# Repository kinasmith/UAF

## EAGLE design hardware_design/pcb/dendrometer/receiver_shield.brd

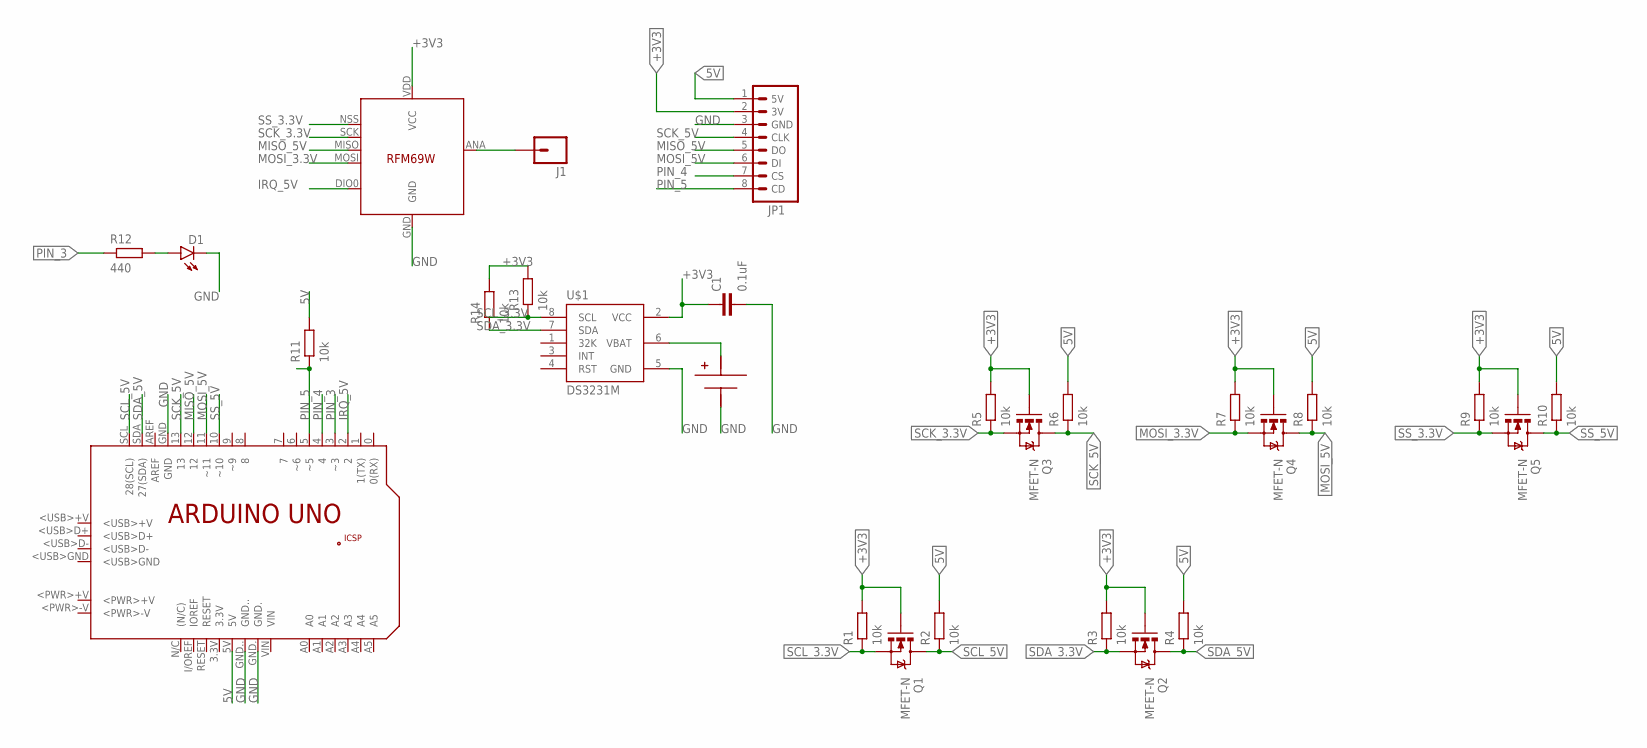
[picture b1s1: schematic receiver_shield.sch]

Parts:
C1: 0.1uF; C0603-N
D1: LED0603; LED-0603
J1: M01NOSILK-KIT; 1X01NS-KIT
JP1: SDCARD_BREAKOUT_HEADER1X08; SD_HEADER
PCB1: ARDUINO_UNO
Q1, Q2, Q3, Q4, Q5: MFET-N; SOT23-3
R1, R2, R3, R4, R5, R6, R7, R8, R9, R10, R11, R13, R14: 10k; R0603-N
R12: 440; R0603-N
U$1: DS3231M; SO08
U$3: LINX_2032BAT_HLDER
U$4: RFM69; RFM69W-MINPADS

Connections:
5V: JP1.1 (5V), PCB1.5V, R2.2, R4.2, R6.2, R8.2, R10.2, R11.2
+3V3: C1.1, JP1.2 (3V), Q1.1 (G), Q2.1 (G), Q3.1 (G), Q4.1 (G), Q5.1 (G), R1.2, R3.2, R5.2, R7.2, R9.2, R13.2, R14.2, U$1.2 (VCC), U$4.VDD (VCC)
GND: C1.2, D1.C, JP1.3 (GND), PCB1.GND, PCB1.GND., PCB1.GND.., U$1.5 (GND), U$3.P$1 (BAT_NEG), U$4.GND; also elsewhere on the board
IRQ_5V: PCB1.2, U$4.DIO0
MISO_5V: JP1.5 (DO), PCB1.12, U$4.MISO
MOSI_3.3V: Q4.2 (S), R7.1, U$4.MOSI
MOSI_5V: JP1.6 (DI), PCB1.11 (~11), Q4.3 (D), R8.1
unnamed: D1.A, R12.2
unnamed 8: U$1.6 (VBAT), U$3.BAT_POS$1 (BAT_POS); also elsewhere on the board
unnamed: J1.1, U$4.ANA (ANT)
PIN_3: PCB1.3 (~3), R12.1
PIN_4: JP1.7 (CS), PCB1.4
PIN_5: JP1.8 (CD), PCB1.5 (~5), R11.1
SCK_3.3V: Q3.2 (S), R5.1, U$4.SCK
SCK_5V: JP1.4 (CLK), PCB1.13, Q3.3 (D), R6.1
SCL_3.3V: Q1.2 (S), R1.1, R13.1, U$1.8 (SCL)
SCL_5V: PCB1.SCL (28(SCL)), Q1.3 (D), R2.1
SDA_3.3V: Q2.2 (S), R3.1, R14.1, U$1.7 (SDA)
SDA_5V: PCB1.SDA (27(SDA)), Q2.3 (D), R4.1
SS_3.3V: Q5.2 (S), R9.1, U$4.NSS (SEL)
SS_5V: PCB1.10 (~10), Q5.3 (D), R10.1

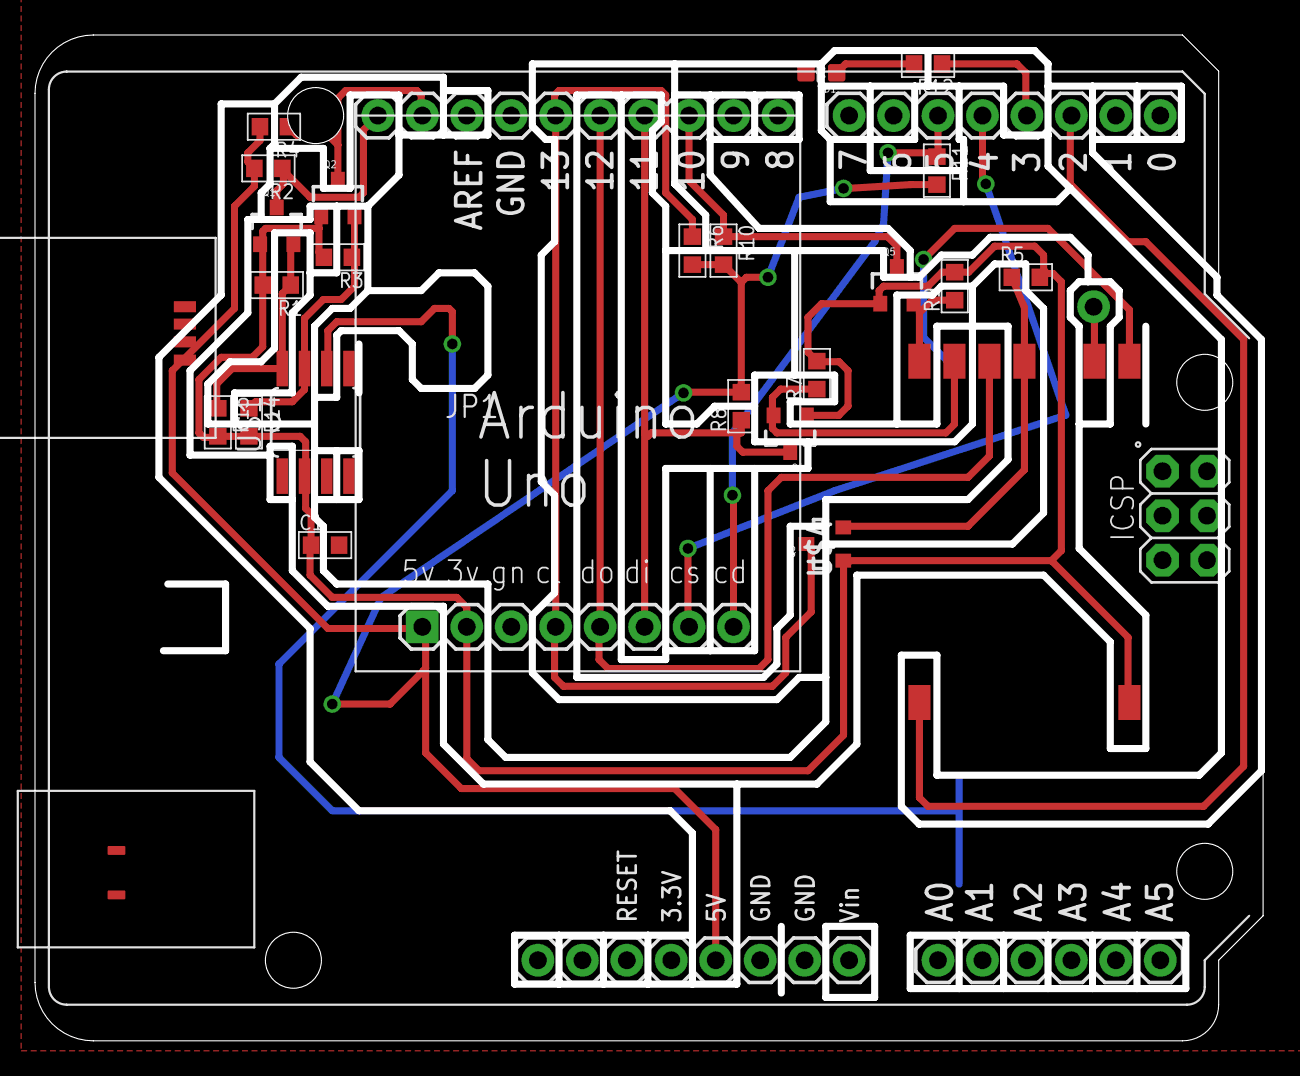
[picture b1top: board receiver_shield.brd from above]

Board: 2 copper layers, 70.2 x 57.5 mm, 27 parts (1 on the bottom side), 21 nets.

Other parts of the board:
U$2: 2032_BAT_HLDR; 2032_BAT_HLDR_MPD

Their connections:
GND: U$2.P$1; also elsewhere on the board
unnamed 8: U$2.P$2; also elsewhere on the board

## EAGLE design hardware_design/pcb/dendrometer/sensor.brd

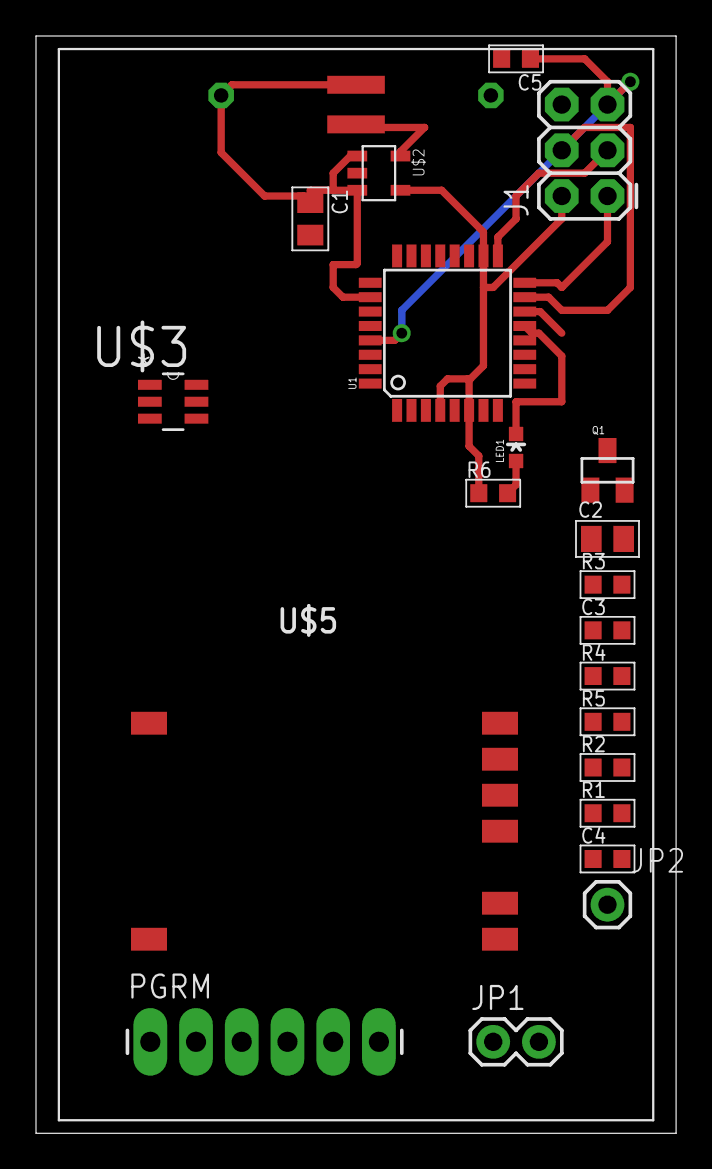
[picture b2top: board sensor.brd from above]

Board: 2 copper layers, 35.6 x 61.0 mm, 23 parts (0 on the bottom side), 22 nets.

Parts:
C1, C2: 10uF; C0805-N
C3, C4, C5: 0.1uF; C0603-N
J1: AVR_SPI_PRG_6PTH; 2X3
JP1: M02PTH; 1X02
JP2: M01PTH; 1X01
LED1: LED-0603
PGRM: 1X06_LONGPADS
Q1: mosfet-N; SOT23
R1, R2, R3, R5, R6: 10k; R0603-N
R4: R0603-N
U1: ATMEGA328P; TQFP32-08
U$1: KEYSTONEAAHOLDER_2CELL
U$2: TPS61097-33; SOT23-5
U$3: MCP3425A0T-E/CH; SOT95P270X145-6N
U$4: INDUCTORS_WURTH; WURTH_10UH_650MA
U$5: RFM69; RFM69W-MINPADS

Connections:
GND: C1.2, C2.2, C4.1, J1.6, JP1.1, PGRM.1, U1.3, U1.5, U1.21, U$1.P$2, U$2.P$2, U$3.2, U$3.6, U$5.GND
MISO: J1.1, U1.16, U$5.MISO
MOSI: J1.4, U1.15, U$5.MOSI
unnamed: U$2.P$5, U$4.P$1
unnamed: C3.1, Q1.1, R3.1
unnamed: JP1.2, R4.1, U$3.1
unnamed: C4.2, U1.20
unnamed: Q1.3, R4.2
unnamed: JP2.1, U$5.ANA
unnamed: LED1.C, U1.13
unnamed: LED1.A, R6.2
unnamed: C5.2, PGRM.6
RST: C5.1, J1.5, R5.1, U1.29
RX: PGRM.4, U1.30
SCK: J1.3, U1.17, U$5.SCK
SCL: R1.1, U1.28, U$3.3
SDA: R2.1, U1.27, U$3.4
SENS_EN: C3.2, U1.2
SS: U1.14, U$5.NSS
TX: PGRM.5, U1.31
V3.3: C2.1, J1.2, Q1.2, R1.2, R2.2, R3.2, R5.2, R6.1, U1.4, U1.6, U1.18, U$2.P$4, U$3.5, U$5.VDD
VBAT: C1.1, U1.26, U$1.P$1, U$2.P$1, U$2.P$3, U$4.P$2

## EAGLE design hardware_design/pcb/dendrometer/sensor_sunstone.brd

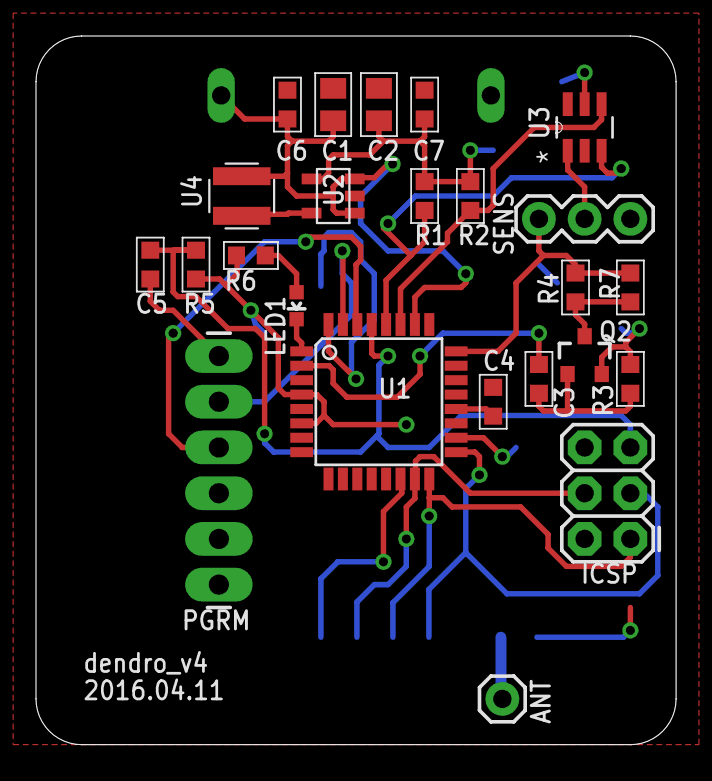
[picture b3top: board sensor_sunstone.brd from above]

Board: 2 copper layers, 35.6 x 39.4 mm, 26 parts (1 on the bottom side), 24 nets.

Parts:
ANT: M01PTH; 1X01
C1, C2: 10uF; C0805-N
C3, C4, C5, C6, C7: 0.1uF; C0603-N
ICSP: AVR_SPI_PRG_6PTH; 2X3
LED1: LED-0603
PGRM: 1X06_LONGPADS
Q2: PFET; SOT23-3
R1, R2, R5, R6: 10k; R0603-N
R3: 1M; R0603-N
R4: 6.8k; R0603-N
R7: 43k; R0603-N
SENS: 1X03
U1: ATMEGA328P; TQFP32-08
U2: TPS61097-33; SOT23-5
U3: MCP3425A0T-E/CH; SOT95P270X145-6N
U4: INDUCTORS_WURTH; WURTH_10UH_650MA
U$1: KEYSTONEAAHOLDER_2CELL
U$5: RFM69; RFM69W-MINPADS

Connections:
G: C3.1, Q2.1, R3.1
GND: C1.2, C2.2, C4.1, C6.2, C7.2, ICSP.6, PGRM.1, SENS.1, U1.3, U1.5, U1.21, U2.P$2, U3.2, U3.6, U$1.P$2, U$5.GND
IRQ: U1.32, U$5.DIO0
MISO: ICSP.1, U1.16, U$5.MISO
MOSI: ICSP.4, U1.15, U$5.MOSI
unnamed: U2.P$5, U4.P$1
unnamed: Q2.3, R4.2, R7.2
unnamed: C4.2, U1.20
unnamed: LED1.C, U1.1
unnamed: SENS.2, U3.1
unnamed: ANT.1, U$5.ANA
unnamed: LED1.A, R6.2
unnamed: C5.2, PGRM.6
RST: C5.1, ICSP.5, R5.1, U1.29
RX: PGRM.4, U1.30
SCK: ICSP.3, U1.17, U$5.SCK
SCL: R1.1, U1.28, U3.3
SDA: R2.1, U1.27, U3.4
SENS_EN: C3.2, U1.2
SS: U1.14, U$5.NSS
TX: PGRM.5, U1.31
V3.3: C2.1, C7.1, ICSP.2, Q2.2, R1.2, R2.2, R3.2, R5.2, R6.1, U1.4, U1.6, U1.18, U2.P$4, U3.5, U$5.VDD
V-EXCITE: R4.1, R7.1, SENS.3, U1.24
VBAT: C1.1, C6.1, U1.26, U2.P$1, U2.P$3, U4.P$2, U$1.P$1

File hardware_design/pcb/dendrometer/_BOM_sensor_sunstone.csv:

"Part";"Value";"Device";"Package";"Description";"";
"ANT";"M01PTH";"M01PTH";"1X01";"Header 1";"";
"C1";"10uF";"CAPACITOR0805-N";"C0805-N";"";"";
"C2";"10uF";"CAPACITOR0805-N";"C0805-N";"";"";
"C3";"0.1uF";"CAPACITOR0603-N";"C0603-N";"";"";
"C4";"0.1uF";"CAPACITOR0603-N";"C0603-N";"";"";
"C5";"0.1uF";"CAPACITOR0603-N";"C0603-N";"";"";
"C6";"0.1uF";"CAPACITOR0603-N";"C0603-N";"";"";
"C7";"0.1uF";"CAPACITOR0603-N";"C0603-N";"";"";
"ICSP";"AVR_SPI_PRG_6PTH";"AVR_SPI_PRG_6PTH";"2X3";"AVR ISP 6 Pin";"";
"LED1";"";"LED0603";"LED-0603";"LEDs";"";
"PGRM";"";"M06LONGPADS";"1X06_LONGPADS";"Header 6";"";
"Q2";"PFET";"MOSFET-PCHANNELIRLML2244";"SOT23-3";"Generic PMOSFET";"";
"R1";"10k";"RESISTOR0603-N";"R0603-N";"";"";
"R2";"10k";"RESISTOR0603-N";"R0603-N";"";"";
"R3";"1M";"RESISTOR0603-N";"R0603-N";"";"";
"R4";"6.8k";"RESISTOR0603-N";"R0603-N";"";"";
"R5";"10k";"RESISTOR0603-N";"R0603-N";"";"";
"R6";"10k";"RESISTOR0603-N";"R0603-N";"";"";
"R7";"43k";"RESISTOR0603-N";"R0603-N";"";"";
"SENS";"";"M03PTH";"1X03";"Header 3";"";
"U$1";"KEYSTONEAAHOLDER_2CELL";"KEYSTONEAAHOLDER_2CELL";"KEYSTONEAAHOLDER_2CELL";"";"";
"U$5";"RFM69";"RFM69";"RFM69W-MINPADS";"";"";
"U1";"ATMEGA328P";"ATMEGA328_SMT";"TQFP32-08";"32-Pin Atmega328 part";"";
"U2";"TPS61097-33";"TPS61097-33";"SOT23-5";"";"";
"U3";"MCP3425A0T-E/CH";"MCP3425A0T-E/CH";"SOT95P270X145-6N";"Analog-to-Digital Converter";"";
"U4";"INDUCTORS_WURTH";"INDUCTORS_WURTH";"WURTH_10UH_650MA";"";"";

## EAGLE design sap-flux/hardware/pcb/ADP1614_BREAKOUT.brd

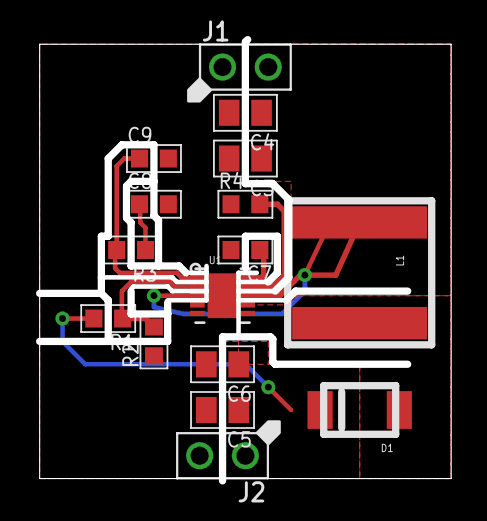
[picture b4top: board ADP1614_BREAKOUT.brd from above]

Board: 2 copper layers, 22.9 x 24.1 mm, 17 parts (0 on the bottom side), 9 nets.

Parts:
C3, C6: 10uF; C0805-N
C4: 10uF 16V; C0805-N
C5: 10uF 25V; C0805-N
C7: 47nF 50v (100nF); C0603-N
C8: 22nF 50v (20nF); C0603-N
C9: 33pF 50v; C0603-N
D1: DIODE-SCHOTTKYSOD128; SOD128
FRAME1: FRAME-LETTER; CREATIVE_COMMONS
J1, J2: MF-CON-2.54mm-01x02; PTH_2.54MM_01X02
L1: 4.7uH 4.3A; L8080
R1: 42.208k (43k); R0603-N
R2: 10k; R0603-N
R3: 2k; R0603-N
R4: 66.5k (68k); R0603-N
U1: ADP1614; DFN300X300X80-11N

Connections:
GND: C3.2, C4.2, C5.2, C6.2, C7.2, C8.2, C9.2, J1.P$1, J2.P$2, R2.1, R4.1, U1.4, U1.5, U1.11
unnamed: R4.2, U1.9
unnamed: C7.1, U1.10
unnamed: C8.1, R3.1
unnamed: C9.1, R3.2, U1.1
unnamed: R1.1, R2.2, U1.2
unnamed: D1.A-2, L1.2, U1.6, U1.7
VIN: C3.1, C4.1, J1.P$2, L1.1, U1.3, U1.8
VOUT: C5.1, C6.1, D1.C-1, J2.P$1, R1.2

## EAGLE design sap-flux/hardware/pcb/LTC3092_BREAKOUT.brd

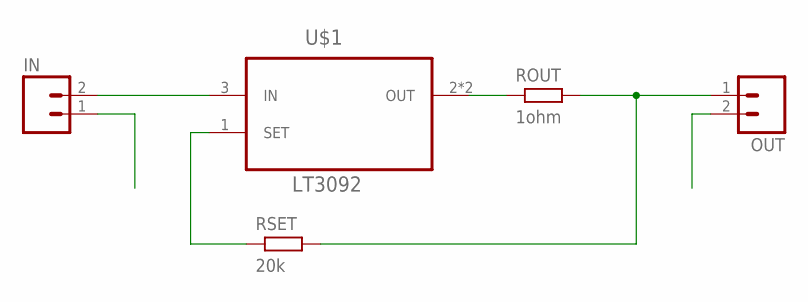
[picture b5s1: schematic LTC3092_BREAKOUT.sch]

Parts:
IN: M02PTH; 1X02
OUT: M02PTH; 1X02
ROUT: 1ohm; R0603-N
RSET: 20k; R0603-N
U$1: LT3092; SOT223

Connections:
GND: IN.1, OUT.2
unnamed: IN.2, U$1.3 (IN)
unnamed: RSET.1, U$1.1 (SET)
unnamed: OUT.1, ROUT.2, RSET.2
unnamed: ROUT.1, U$1.2 (OUT), U$1.4 (OUT)

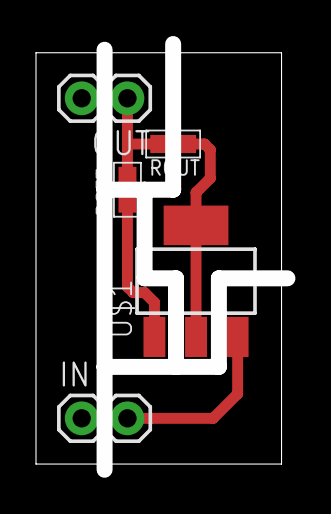
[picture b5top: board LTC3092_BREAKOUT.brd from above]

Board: 2 copper layers, 13.6 x 22.9 mm, 5 parts (0 on the bottom side), 5 nets.

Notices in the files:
parts and their libraries:
SparkFun-DiscreteSemi: Licensing: Creative Commons ShareAlike 4.0 International - https://creativecommons.org/licenses/by-sa/4.0
SparkFun-Connectors: Licensing: CC v3.0 Share-Alike You are welcome to use this library for commercial purposes.
